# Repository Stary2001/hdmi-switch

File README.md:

## USB controlled HDMI Switch

I couldn't find one of these easily, so I decided to make one myself.

This uses a PI3HDX621 `3.4Gbps HDMI1.4b Active 2:1 Switch with ARC and Fast Switching` paired with a SAMD21 microcontroller (because I had some in stock).

The firmware is implemented with my library [libsam](https://github.com/Stary2001/libsam).

Untested things - the switch IC supports ARC, but I didn't test that yet because I don't have anything handy that supports it.

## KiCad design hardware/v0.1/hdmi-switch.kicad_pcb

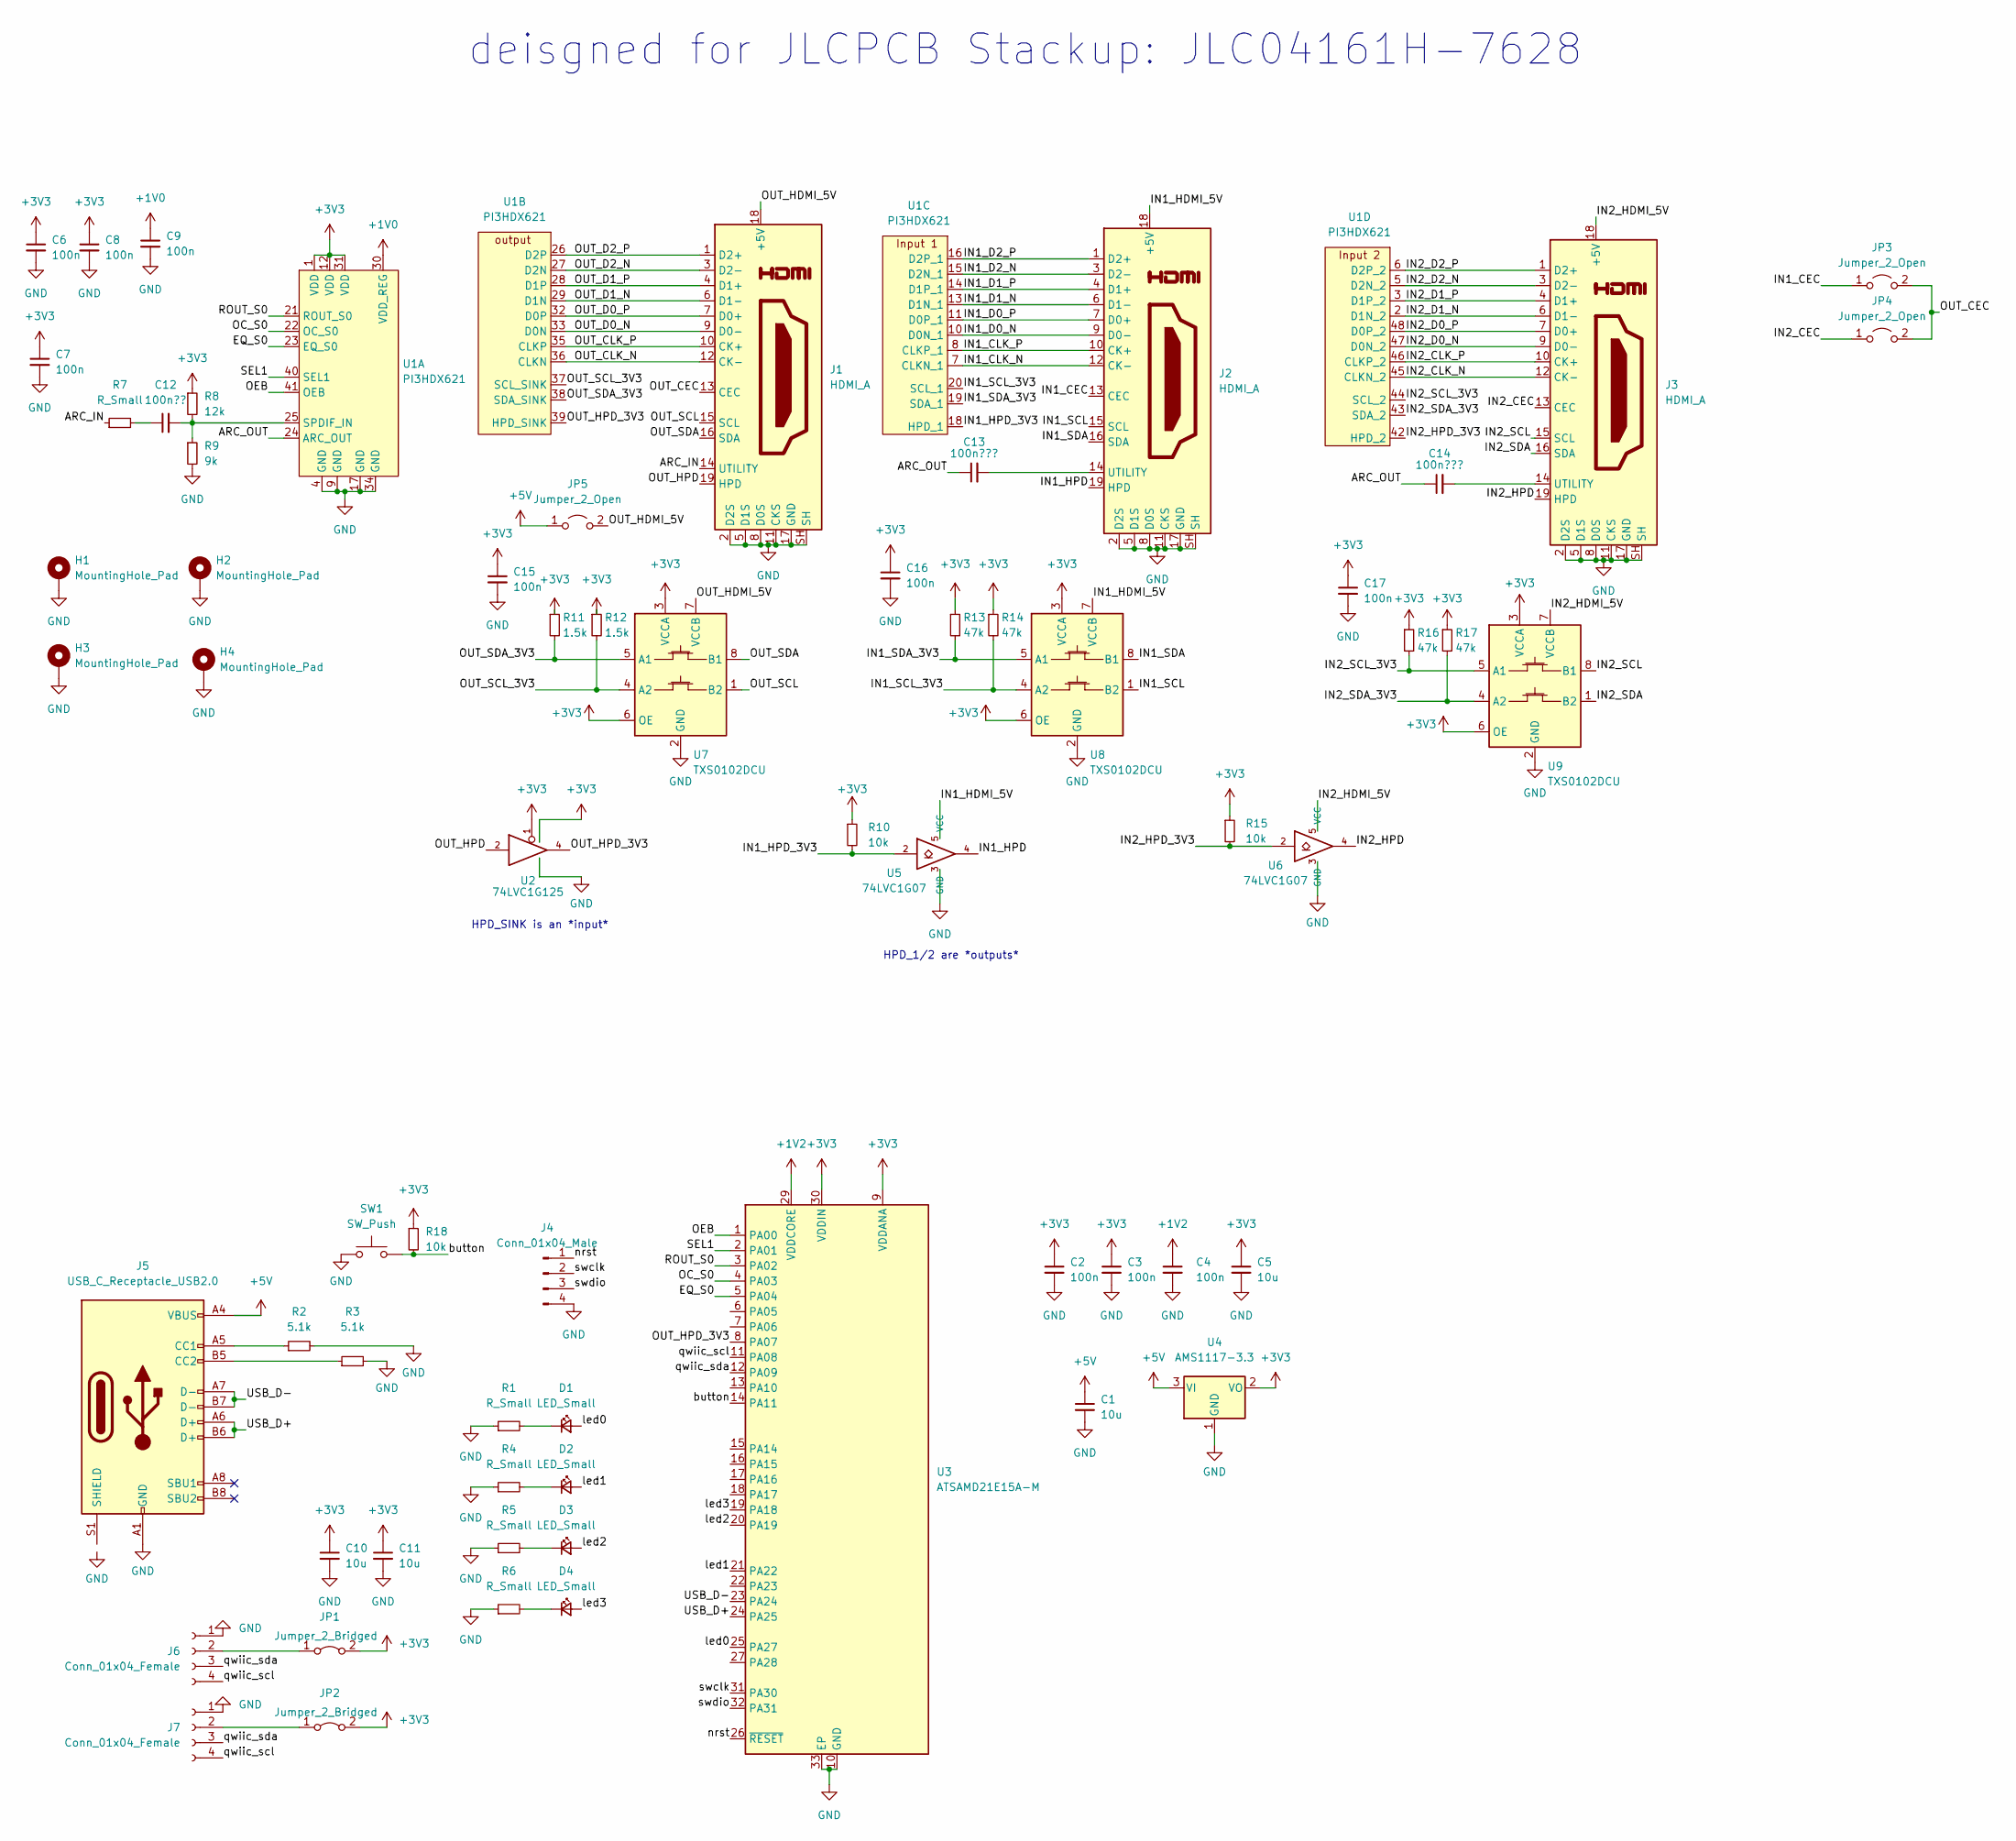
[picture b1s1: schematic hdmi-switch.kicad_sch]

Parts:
C1, C5, C10, C11: 10u; C_0603_1608Metric
C2, C3, C4, C6, C7, C8, C15, C16, C17: 100n; C_0402_1005Metric
C9: 100n; C_0603_1608Metric
C12: 100n??; C_0603_1608Metric
C13, C14: 100n???; C_0402_1005Metric
D1, D2, D3, D4: LED_Small; LED_0603_1608Metric
H1, H2, H3, H4: MountingHole_Pad; MountingHole_3.2mm_M3_Pad_Via
J1, J2, J3: HDMI_A; HDMI-SS-53000
J4: Conn_01x04_Male; PinHeader_1x04_P2.54mm_Vertical
J5: USB_C_Receptacle_USB2.0; USB_C_Receptacle_HRO_TYPE-C-31-M-12
J6, J7: Conn_01x04_Female; JST_SH_SM04B-SRSS-TB_1x04-1MP_P1.00mm_Horizontal
JP1, JP2: Jumper_2_Bridged; SolderJumper-2_P1.3mm_Open_RoundedPad1.0x1.5mm
JP3, JP4, JP5: Jumper_2_Open; SolderJumper-2_P1.3mm_Open_RoundedPad1.0x1.5mm
R1, R4, R5, R6, R7: R_Small; R_0603_1608Metric
R2, R3: 5.1k; R_0603_1608Metric
R8: 12k; R_0603_1608Metric
R9: 9k; R_0603_1608Metric
R10, R15, R18: 10k; R_0603_1608Metric
R11, R12: 1.5k; R_0603_1608Metric
R13, R14, R16, R17: 47k; R_0603_1608Metric
SW1: SW_Push; PTS636
U1: PI3HDX621; LQFP-48_7x7mm_P0.5mm
U2: 74LVC1G125; SOT-23-5
U3: ATSAMD21E15A-M; QFN-32-1EP_5x5mm_P0.5mm_EP3.6x3.6mm
U4: AMS1117-3.3; SOT-223-3_TabPin2
U5, U6: 74LVC1G07; SOT-23-5
U7, U8, U9: TXS0102DCU; VSSOP-8_2.3x2mm_P0.5mm

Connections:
+1V0: C9.1, U1.30 (VDD_REG)
+1V2: C4.1, U3.29 (VDDCORE)
+3V3: C2.1, C3.1, C5.1, C6.1, C7.1, C8.1, C10.1, C11.1, C15.1, C16.1, C17.1, JP1.2 (B), JP2.2 (B), R8.1, R10.1, R11.1, R12.1, R13.1, R14.1, R15.1, R16.1, R17.1, R18.1, U1.1 (VDD), U1.12 (VDD), U1.31 (VDD), U2.1, U2.5 (VCC), U3.9 (VDDANA), U3.30 (VDDIN), U4.2 (VO), U7.3 (VCCA), U7.6 (OE), U8.3 (VCCA), U8.6 (OE), U9.3 (VCCA), U9.6 (OE)
+5V: C1.1, J5.A4 (VBUS), J5.A9 (VBUS), J5.B4 (VBUS), J5.B9 (VBUS), JP5.1 (A), U4.3 (VI)
/ARC_IN: J1.14 (UTILITY), R7.1
/ARC_OUT: C13.1, C14.1, U1.24 (ARC_OUT)
/EQ_S0: U1.23 (EQ_S0), U3.5 (PA04)
/IN1_CEC: J2.13 (CEC), JP3.1 (A)
/IN1_CLK_N: J2.12 (CK-), U1.7 (CLKN_1)
/IN1_CLK_P: J2.10 (CK+), U1.8 (CLKP_1)
/IN1_D0_N: J2.9 (D0-), U1.10 (D0N_1)
/IN1_D0_P: J2.7 (D0+), U1.11 (D0P_1)
/IN1_D1_N: J2.6 (D1-), U1.13 (D1N_1)
/IN1_D1_P: J2.4 (D1+), U1.14 (D1P_1)
/IN1_D2_N: J2.3 (D2-), U1.15 (D2N_1)
/IN1_D2_P: J2.1 (D2+), U1.16 (D2P_1)
/IN1_HDMI_5V: J2.18 (+5V), U5.5 (VCC), U8.7 (VCCB)
/IN1_HPD: J2.19 (HPD), U5.4
/IN1_HPD_3V3: R10.2, U1.18 (HPD_1), U5.2
/IN1_SCL: J2.15 (SCL), U8.1 (B2)
/IN1_SCL_3V3: R14.2, U1.20 (SCL_1), U8.4 (A2)
/IN1_SDA: J2.16 (SDA), U8.8 (B1)
/IN1_SDA_3V3: R13.2, U1.19 (SDA_1), U8.5 (A1)
/IN2_CEC: J3.13 (CEC), JP4.1 (A)
/IN2_CLK_N: J3.12 (CK-), U1.45 (CLKN_2)
/IN2_CLK_P: J3.10 (CK+), U1.46 (CLKP_2)
/IN2_D0_N: J3.9 (D0-), U1.47 (D0N_2)
/IN2_D0_P: J3.7 (D0+), U1.48 (D0P_2)
/IN2_D1_N: J3.6 (D1-), U1.2 (D1N_2)
/IN2_D1_P: J3.4 (D1+), U1.3 (D1P_2)
/IN2_D2_N: J3.3 (D2-), U1.5 (D2N_2)
/IN2_D2_P: J3.1 (D2+), U1.6 (D2P_2)
/IN2_HDMI_5V: J3.18 (+5V), U6.5 (VCC), U9.7 (VCCB)
/IN2_HPD: J3.19 (HPD), U6.4
/IN2_HPD_3V3: R15.2, U1.42 (HPD_2), U6.2
/IN2_SCL: J3.15 (SCL), U9.8 (B1)
/IN2_SCL_3V3: R16.2, U1.44 (SCL_2), U9.5 (A1)
/IN2_SDA: J3.16 (SDA), U9.1 (B2)
/IN2_SDA_3V3: R17.2, U1.43 (SDA_2), U9.4 (A2)
/OC_S0: U1.22 (OC_S0), U3.4 (PA03)
/OEB: U1.41 (OEB), U3.1 (PA00)
/OUT_CEC: J1.13 (CEC), JP3.2 (B), JP4.2 (B)
/OUT_CLK_N: J1.12 (CK-), U1.36 (CLKN)
/OUT_CLK_P: J1.10 (CK+), U1.35 (CLKP)
/OUT_D0_N: J1.9 (D0-), U1.33 (D0N)
/OUT_D0_P: J1.7 (D0+), U1.32 (D0P)
/OUT_D1_N: J1.6 (D1-), U1.29 (D1N)
/OUT_D1_P: J1.4 (D1+), U1.28 (D1P)
/OUT_D2_N: J1.3 (D2-), U1.27 (D2N)
/OUT_D2_P: J1.1 (D2+), U1.26 (D2P)
/OUT_HDMI_5V: J1.18 (+5V), JP5.2 (B), U7.7 (VCCB)
/OUT_HPD: J1.19 (HPD), U2.2
/OUT_HPD_3V3: U1.39 (HPD_SINK), U2.4, U3.8 (PA07)
/OUT_SCL: J1.15 (SCL), U7.1 (B2)
/OUT_SCL_3V3: R12.2, U1.37 (SCL_SINK), U7.4 (A2)
/OUT_SDA: J1.16 (SDA), U7.8 (B1)
/OUT_SDA_3V3: R11.2, U1.38 (SDA_SINK), U7.5 (A1)
/ROUT_S0: U1.21 (ROUT_S0), U3.3 (PA02)
/SEL1: U1.40 (SEL1), U3.2 (PA01)
/USB_D+: J5.A6 (D+), J5.B6 (D+), U3.24 (PA25)
/USB_D-: J5.A7 (D-), J5.B7 (D-), U3.23 (PA24)
/button: R18.2, SW1.2, U3.14 (PA11)
/led0: D1.2 (A), U3.25 (PA27)
/led1: D2.2 (A), U3.21 (PA22)
/led2: D3.2 (A), U3.20 (PA19)
/led3: D4.2 (A), U3.19 (PA18)
/nrst: J4.1, U3.26 (~RESET)
/qwiic_scl: J6.4, J7.4, U3.11 (PA08)
/qwiic_sda: J6.3, J7.3, U3.12 (PA09)
/swclk: J4.2, U3.31 (PA30)
/swdio: J4.3, U3.32 (PA31)
GND: C1.2, C2.2, C3.2, C4.2, C5.2, C6.2, C7.2, C8.2, C9.2, C10.2, C11.2, C15.2, C16.2, C17.2, H1.1, H2.1, H3.1, H4.1, J1.2 (D2S), J1.5 (D1S), J1.8 (D0S), J1.11 (CKS), J1.17 (GND), J1.SH, J2.2 (D2S), J2.5 (D1S), J2.8 (D0S), J2.11 (CKS), J2.17 (GND), J2.SH, J3.2 (D2S), J3.5 (D1S), J3.8 (D0S), J3.11 (CKS), J3.17 (GND), J3.SH, J4.4, J5.A1 (GND), J5.A12 (GND), J5.B1 (GND), J5.B12 (GND), J6.1, J7.1, R1.1, R2.2, R3.2, R4.1, R5.1, R6.1, R9.2, SW1.1, U1.4 (GND), U1.9 (GND), U1.17 (GND), U1.34 (GND), U2.3 (GND), U3.10 (GND), U3.28 (GND), U3.33 (EP), U4.1 (GND), U5.3 (GND), U6.3 (GND), U7.2 (GND), U8.2 (GND), U9.2 (GND)
unnamed: C12.1, R7.2
unnamed: C12.2, R8.2, R9.1, U1.25 (SPDIF_IN)
unnamed: C13.2, J2.14 (UTILITY)
unnamed: C14.2, J3.14 (UTILITY)
unnamed: D1.1 (K), R1.2
unnamed: D2.1 (K), R4.2
unnamed: D3.1 (K), R5.2
unnamed: D4.1 (K), R6.2
unnamed: J5.A5 (CC1), R2.1
unnamed: J5.B5 (CC2), R3.1
unnamed: J6.2, JP1.1 (A)
unnamed: J7.2, JP2.1 (A)

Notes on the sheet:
deisgned for JLCPCB Stackup: JLC04161H-7628
HPD_SINK is an *input*
HPD_1/2 are *outputs*

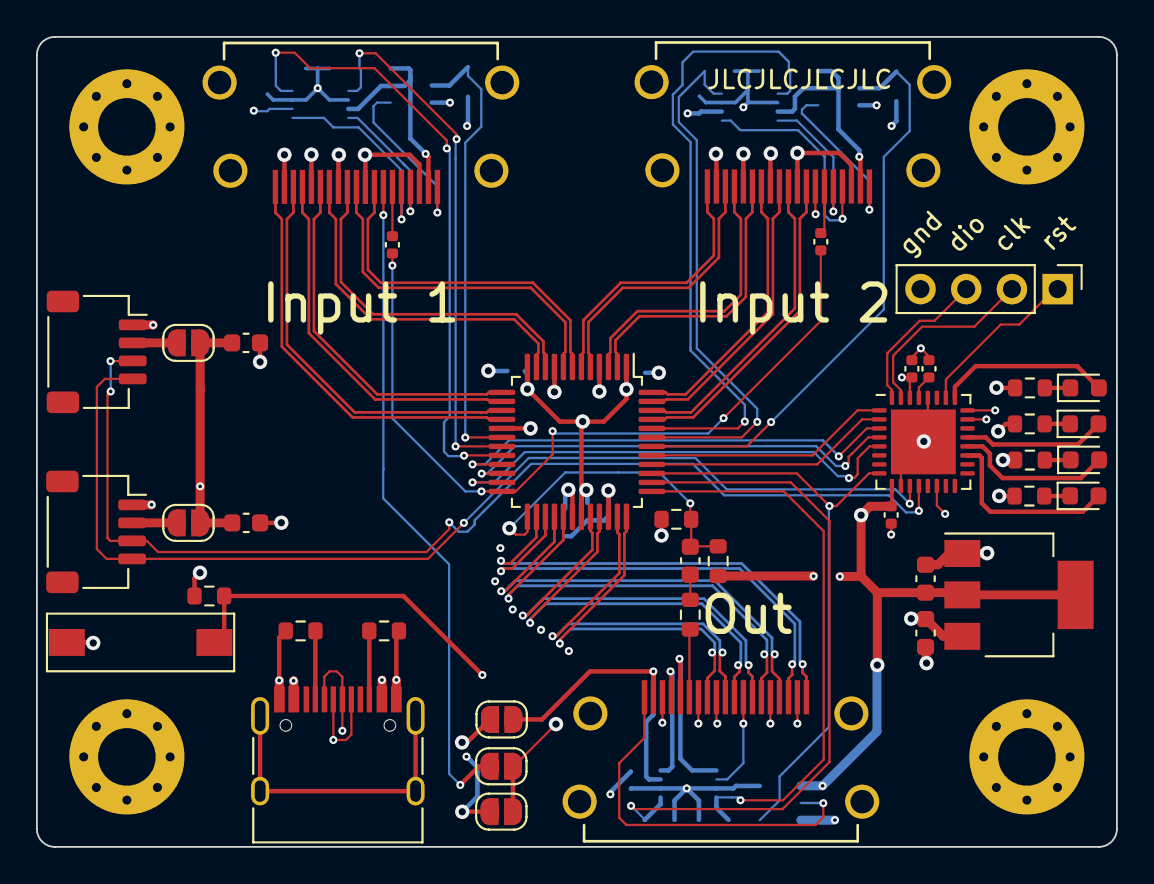
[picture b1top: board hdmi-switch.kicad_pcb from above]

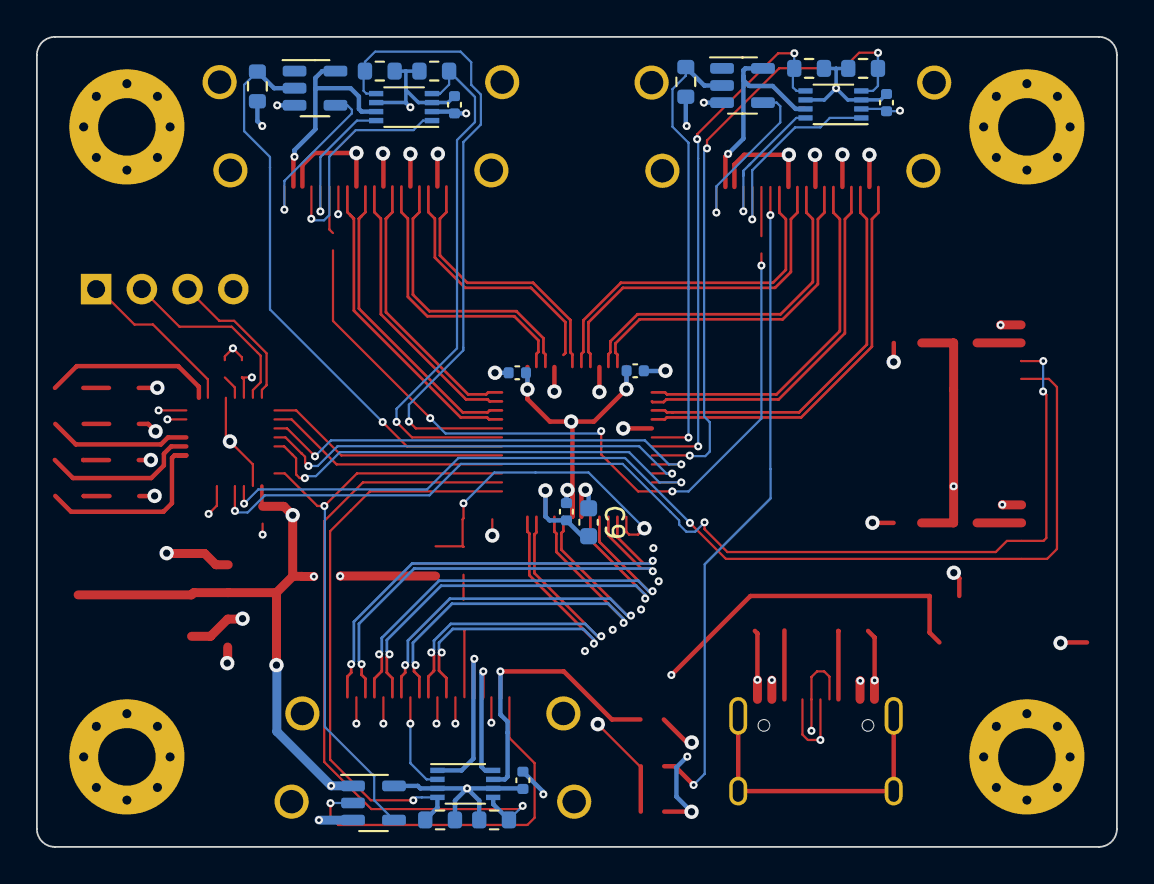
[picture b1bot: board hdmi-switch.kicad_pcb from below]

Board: 4 copper layers, 60.0 x 45.0 mm, 65 parts (21 on the bottom side), 84 nets.

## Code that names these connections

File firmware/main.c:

#include <stdio.h>
#include "sam/gpio.h"
#include "sam/bod.h"
#include "sam/clock.h"
#include "sam/sercom_usart.h"
#include "sam/pinmux.h"
#include "sam/serial_number.h"

#include "tusb.h"

void USB_Handler() {
	tud_int_handler(0);
}

volatile uint32_t system_ticks = 0;
void SysTick_Handler (void)
{
	system_ticks++;
}

// GPIO pin definitions
const int OE_B = 0;
const int SEL1 = 1;
const int ROUT_S0 = 2;
const int OC_S0 = 3;
const int EQ_S0 = 4;

const int HPD_IN = 7;

const int LED0 = 27;
const int LED1 = 22;
const int LED2 = 19;
const int LED3 = 18;

const int BUTTON = 11;

bool current_output = true;
static void switch_to_output(bool out) {
	current_output = out;
	if(current_output) {
		port_set_value(1, true);
		port_set_value(LED0, true);
		port_set_value(LED3, false);
	} else {
		port_set_value(1, false);
		port_set_value(LED0, false);
		port_set_value(LED3, true);
	}
}

static void cdc_task(void) {
	if (tud_cdc_n_available(0)) {
		uint8_t buf[64];
		uint32_t count = tud_cdc_n_read(0, buf, sizeof(buf));

		for(uint32_t i = 0; i < count; i++) {
			if(buf[i] == '1') {
				switch_to_output(true); // switch to 1
			} else if(buf[i] == '2') {
				switch_to_output(false); // switch to 2
			}
		}
	}
}

static void button_task(void) {
	static int last_tick = 0;
	static bool waiting_for_low = false;

	bool button_value = !port_get_value(BUTTON);
	if(button_value && !waiting_for_low) {
		if(system_ticks - last_tick > 100) {
			last_tick = system_ticks;
			waiting_for_low = true;
			switch_to_output(!current_output);
		}
	} else if(!button_value) {
		waiting_for_low = false;
	}
}

extern char const* string_desc_arr [];

int main() {
	clock_switch_to_8mhz();
	bod_init();
	bod_set_3v3();

	clock_switch_to_48mhz_from_usb();
	clock_setup_gclk2_8mhz();
	clock_setup_usb();

	clock_setup_systick_1ms();

	port_set_direction(OE_B, true);
	port_set_direction(SEL1, true);
	port_set_direction(ROUT_S0, true);
	port_set_direction(OC_S0, true);
	port_set_direction(EQ_S0, true);

	port_set_direction(HPD_IN, false);

	port_set_direction(LED0, true);
	port_set_direction(LED1, true);
	port_set_direction(LED2, true);
	port_set_direction(LED3, true);

	port_set_value(LED0, true);
	port_set_value(LED1, false);
	port_set_value(LED2, false);
	port_set_value(LED3, false);

	port_set_direction(BUTTON, false);

	port_set_value(OE_B, false); // oeb low = enable
	port_set_value(SEL1, true); // sel1 high = port 1 select
	port_set_value(ROUT_S0, true); // rout_s0 high = 50ohm termination
	port_set_value(OC_S0, false); // low = 0db pre-emphasis
	port_set_value(EQ_S0, false); // low = 9db eq

	pinmux_setup_usb();

	string_desc_arr[3] = (const char *) serial_get_hash_hex();

	tusb_init();
	tud_init(0);

	while(true) {
		tud_task();
		cdc_task();
		button_task();
	}

	return 0;
}

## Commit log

2023-01-05 use wrap for libsam
2023-01-05 fix indentation, cleanup
2023-01-07 update firmware - enable systick so button actually works
2023-01-07 more cleanup
2023-01-07 add README
2023-05-10 add gitignore, move hardware to 0.1
